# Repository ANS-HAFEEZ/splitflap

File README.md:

# Split-Flap Display

This is a DIY ESP32-based [split-flap display](https://en.wikipedia.org/wiki/Split-flap_display), optimized for easy assembly at home in small quantities but able to be scaled up to large affordable displays.

The [splitflap community Discord server](https://discord.com/invite/wgehm3PcrC) is the best place to keep up with the latest changes or ask questions about the project!

Want to help support development or just say "thanks"? Consider a one-time or monthly sponsorship:

| [:heart: Sponsor scottbez1 on GitHub](https://github.com/sponsors/scottbez1) |
|---|

**Using this project in a commercial setting or for paid client work?** Go right ahead - it's open source (just make sure to follow the terms of the Apache License)! I would, however, ask that you consider [sponsoring the project](https://github.com/sponsors/scottbez1). I've been developing and maintaining this project in my free time for over 10 years, and I'd love to continue working on it. Sponsorships allow me to pay for prototypes and development tools that make this project possible. Unlike pure software projects, every iteration has real hardware costs; sponsorships allow me to keep iterating and improving the project faster. Thank you!

# Current Status
[You can download the **latest stable releases** of the hardware designs from the official 'releases' page.](https://github.com/scottbez1/splitflap/releases)

Releases have been tested and used to produce working units, but as this is a continuously evolving open-source project, there may always be minor issues and/or incomplete documentation from time to time.

Here's a video of a large 108-module display powered by 18 Chainlink Driver boards and a Chainlink Base:

## Stable v2 Mechanical Release
As of 2025-01-19, the v2 refresh of the mechanical and sensor design is considered stable and recommended for new builds.

**Here's what's new in v2:**

- **40 flaps per module is the default configuration in this repository**
- **52-flap v2 modules remain supported** if you want additional symbols/color blocks
- **New printed flap design ("Epilogue")** with 52 flaps per set (see animation above), including several color-block flaps
- **Updated enclosure** and mechanical parts (laser-cut) to accomodate both 40- and 52-flap variants
  - Motor wires now exit downward for less awkward wiring!
- **New sensor PCB** that's easier to assemble and includes an LED for checking the magnet status
- **Software-configurable calibration** rather than mechanical sensor adjustment

**But many things are staying the same for easy upgrades/compatibility:**
- No change to flap dimensions!
- No changes to Chainlink Driver, Chainlink Buddy boards, or system architecture!
- 52-flap modules are still an officially supported option!
- Open source, as always!
- v0 parts (sensor kits) will continue to be stocked at Bezek Labs through mid-2025; don't worry if you haven't finished your build yet, the old sensor kits aren't going away for a little while!

I'd love to hear your thoughts and questions about this project, and happy to incorporate any feedback you might have into these designs! Please feel free (and encouraged) to [open GitHub issues](https://github.com/scottbez1/splitflap/issues/new), email me directly, reach out [on Bluesky](https://bsky.app/profile/scottbez1.bsky.social), and [get involved](https://github.com/scottbez1/splitflap/pulls) in the open source development and let's keep chatting and building together!

# Build Your Own
If you have any questions, please don't hesitate to ask in the [community Discord server](https://discord.gg/Hxnftc8PyW)!

* [**Documentation Index**](/docs/DocumentationIndex.md)
* [**Ordering guide (the "easy" route) v2**](/docs/v2/OrderingEasy.md)
* [**Comprehensive ordering guide**](/docs/v2/OrderingComplete.md)
* [**Chainlink Driver Electronics User Guide**](/docs/ElectronicsGuide.md)
* [**Assembly instructions v2**](/docs/v2/Assembly.md)
* [**Latest stable releases**](https://github.com/scottbez1/splitflap/releases)

# Table of Contents
- [Design Overview](#design-overview)
  - [Mechanical](#mechanical)
    - [Combined front panel (script)](#combined-front-panel-script)
    - [Flap font/sticker generator (script)](#flap-fontsticker-generator-script)
  - [Electronics](#electronics)
    - [Sensor PCBs](#sensor-pcbs-1-per-module)
    - [Chainlink Driver](#chainlink-driver-1-per-6-modules)
    - [Chainlink Buddy \[T-Display\]](#chainlink-buddy-t-display-1-for-entire-display)
    - [Advanced items](#advanced-items)
      - [Chainlink Buddy \[Breadboard\]](#chainlink-buddy-breadboard-1-for-entire-display-alternative-to-t-display)
      - [Chainlink Base](#chainlink-base-1-for-entire-display-large-displays)
    - [Older designs](#older-designs)
      - [Classic controller](#classic-controller-electronics-deprecated)
    + [Miscellaneous Tools](#miscellaneous-tools)
      - [3D Printed Tools](#3d-printed-tools)
      - [Chainlink Driver Tester](#chainlink-driver-tester)
  * [Code](#code)
    + [Firmware](#firmware)
    + [Computer Control Software](#computer-control-software)
- [Contributing/Modifying](#contributingmodifying)
  * [3D Design](#3d-design)
  * [Electronics Design](#electronics-design)

# Design Overview

## Mechanical
The mechanical/structural components are made from laser-cut 3mm MDF or acrylic, and held together with M4 bolts and nuts. The design is parametric and built using OpenSCAD. See below for more info on rendering/modifying the design.

You can view an interactive 3d model of the design [here](https://scottbez1.github.io/splitflap/embed.html?branch=master).

The v2 mechanical design officially supports both 40- and 52-flap variants (52 is perfect for use with the new ["Epilogue" printed flaps](https://bezeklabs.etsy.com/listing/1685633114/)). Repository defaults are configured for 40 flaps, but you can always override this.

### v2 (52-flap module option)

Instructions: [v2 assembly guide](/docs/v2/Assembly.md)

Module dimensions: 

Latest auto-generated (untested!) artifacts<sup>:warning:</sup>:
* For Ponoko 3mm MDF ([svg](https://s3.amazonaws.com/splitflap-artifacts/master/3d/3d_laser_vector-52-ponoko-3mm-mdf_1x.svg)) 
* For Ponoko 3mm acrylic ([svg](https://s3.amazonaws.com/splitflap-artifacts/master/3d/3d_laser_vector-52-ponoko-3mm-acrylic_1x.svg)) 
* For generic material (0.18mm kerf correction) ([svg](https://s3.amazonaws.com/splitflap-artifacts/master/3d/3d_laser_vector-52.svg))
* For Elecrow 3mm Wood ([zipped pdf](https://s3.amazonaws.com/splitflap-artifacts/master/3d/3d_laser_vector-52-elecrow-3mm-wood_1x.zip))
* For Elecrow 3mm Acrylic ([zipped pdf](https://s3.amazonaws.com/splitflap-artifacts/master/3d/3d_laser_vector-52-elecrow-3mm-acrylic_1x.zip))

<sup>:warning:</sup>For tested/stable/recommended artifacts, always use the [latest release](https://github.com/scottbez1/splitflap/releases) instead, as the links on this page will change over time.

### v2 (40-flap module option - default)

Instructions: [v2 assembly guide](/docs/v2/Assembly.md)

Module dimensions: 

Latest auto-generated (untested!) artifacts<sup>:warning:</sup>:
* For Ponoko 3mm MDF ([svg](https://s3.amazonaws.com/splitflap-artifacts/master/3d/3d_laser_vector-40-ponoko-3mm-mdf_1x.svg)) 
* For Ponoko 3mm acrylic ([svg](https://s3.amazonaws.com/splitflap-artifacts/master/3d/3d_laser_vector-40-ponoko-3mm-acrylic_1x.svg)) 
* For generic material (0.18mm kerf correction) ([svg](https://s3.amazonaws.com/splitflap-artifacts/master/3d/3d_laser_vector-40.svg))
* For Elecrow 3mm Wood ([zipped pdf](https://s3.amazonaws.com/splitflap-artifacts/master/3d/3d_laser_vector-40-elecrow-3mm-wood_1x.zip))
* For Elecrow 3mm Acrylic ([zipped pdf](https://s3.amazonaws.com/splitflap-artifacts/master/3d/3d_laser_vector-40-elecrow-3mm-acrylic_1x.zip))

<sup>:warning:</sup>For tested/stable/recommended artifacts, always use the [latest release](https://github.com/scottbez1/splitflap/releases) instead, as the links on this page will change over time.

### Combined front panel (script)
By default, the design will have a separate laser-cut faceplate for each individual module. For larger displays you may want to combine front panels into a single piece, and the repo has a script to help with this.

You can modify:
* Number of rows and columns
* Horizontal and vertical spacing/separation of modules
* Overall outer width and height of the panel

There are a lot of options; see the `--help` for explanations.

#### Example 1 - Laser cut 6x1

```
python3 3d/scripts/generate_combined_front_panel.py \
  --kerf-preset elecrow-3mm-acrylic \
  --num-flaps 40 \
  --cols 6 \
  --rows 1 \
  --spacing-x 0 \
  --spacing-y 0 \
  --frame-margin-x 0 \
  --frame-margin-y 0 \
  --center-mode module
```

#### Example 2 - CNC router 12x2, with frame margin

For CNC cutting, the script supports rendering a vector file optimized for thicker material (e.g. 6mm MDF) where only the bolt-holes will be through-cut. In this mode, the slots for the top/bottom enclosure pieces can be cut as ~4mm pockets so they aren't visible from the front face. The script automatically generates dog-bone shapes for these pocket cuts.

This example also demonstrates use of the --frame-margin-x and --frame-margin-y options to add an additional margin of 20mm horizontally and 4mm vertically to the front panel dimensions.

```
python3 3d/scripts/generate_combined_front_panel.py \
  --tool-diameter 3.175 \
  --num-flaps 40 \
  --cols 12 \
  --rows 2 \
  --spacing-x 0 \
  --spacing-y 0 \
  --frame-margin-x 20 \
  --frame-margin-y 4 \
  --center-mode module
```

### Flap font/sticker generator (script)
If you'd like to print your own flaps, or cut custom vinyl letter stickers, the project includes a script (`generate_fonts.py`) to generate vector design files, which is extremely configurable:

* Font for text
  * This is further customizable in `flap_fonts.scad` -- this is where font parameters are defined like the overall font scale, position offsets, and even per-character scale and position overrides in case you need to tweak particularly problematic letters (e.g. a really wide "W" or an "@" with too thin of a stroke).
* Character-set - which letters/numbers/symbols/colors are included and in what order
* Bleed - extends rendering past the borders of the flaps to compensate for slight misalignment of printing and cutting operations
* Keepout areas - option to highlight keepout violations for manual review, automatically clip them, or ignore them
* Rendering options:
    * Single-sided - useful for previewing how all letters will look on flaps
    * Front/back - for batch duplex printing, generate separate front-side and back-side files (e.g. sign shop printing on a flat sheet of PVC)
    * Side-by-side - for individual flap printing, each flap's front design is laid out side-by-side with its back design

There are a lot of options; see the `--help` for explanations.

#### Example 1 - Epilogue font, rendered in front+back pairs, default character set, 1mm bleed (for printing)

```
python3 3d/scripts/generate_fonts.py \
  --mode side-by-side \
  --font Epilogue \
  --columns 4 \
  --bleed 1 \
  --fill
```

## Electronics
> [!NOTE]
> For small displays (up to 3 modules), you can skip the custom controller boards and use off-the-shelf ULN2003A driver
modules plugged into an Arduino Uno. This is [partially documented in the wiki](https://github.com/scottbez1/splitflap/wiki/Electronics#basic-prototyping-alternative-electronics-approach)
> but may require some additional tinkering to get it to work. _Help wanted: if you'd like to help improve these instructions,
> please reach out in the Discord server, thanks!_

The "Chainlink" electronics system is designed to support long chains of driver boards to control medium/large displays (up to 100+ split-flap modules).
It's also designed to be easy and cheap to order pre-assembled or build yourself, especially in higher
quantities, due to its simple BOM and surface-mount components.

To build a display, you'll need 3 different electronics:
* One **Sensor PCB** for every split-flap module
* One **Chainlink Driver** board for every 6 split-flap modules. This is what interfaces with the motors and sensors of each module. Chainlink Driver boards can be chained together to construct a large display.
* An ESP32 microcontroller board. There are a few options:
    * For small/medium displays, one of the **Chainlink Buddy** boards are recommended
        * **Chainlink Buddy [T-Display]**  holds a Lilygo T-Display ESP32 module which includes a built-in LCD and 2 buttons
        * **Chainlink Buddy [Breadboard]** makes it easy to connect a Chainlink Driver to a breadboard for prototyping, though you can also easily connect a Chainlink Driver to a breadboard with a few dupont wires.
    * For large displays, the **Chainlink Base** provides a number of advanced features: central
power management/distribution and fault monitoring, UART and RS-485 connections, configuration switches, and status LEDs.

### Sensor PCBs (1 per module)
Each module needs a hall-effect sensor for start-up calibration and fault monitoring. 

#### Sensors v2

New sensors for the v2 laser-cut hardware - these use surface mount components and are optimized for PCB assembly at JLCPCB. These new sensors are not compatible with v0.7 and older laser-cut hardware.

Packs of 6 sensors are [available mostly-assembled in the Bezek Labs store](https://bezeklabs.etsy.com/listing/1696745674),
and come with the right-angle pin headers and magnets you'll need. Purchases support continued development of this project.

Latest auto-generated (untested!) artifacts<sup>:warning:</sup>:

* Schematic [pdf](https://s3.amazonaws.com/splitflap-artifacts/master/electronics-v2/sensor_smd-schematic.pdf)
* Interactive BOM (for manual assembly) [interactive](https://s3.amazonaws.com/splitflap-artifacts/master/electronics-v2/sensor_smd-ibom.html)
* Fabrication files (single)
  * NOTE: PCBs must be 0.8mm! (rather than the more typical 1.6mm thickness)
  * PCB gerbers [zip](https://s3.amazonaws.com/splitflap-artifacts/master/electronics-v2/sensor_smd-jlc/gerbers.zip)
  * PCB BOM (for JLCPCB assembly) [csv](https://s3.amazonaws.com/splitflap-artifacts/master/electronics-v2/sensor_smd-jlc/bom.csv)
  * PCB CPL (for JLCPCB assembly) [csv](https://s3.amazonaws.com/splitflap-artifacts/master/electronics-v2/sensor_smd-jlc/pos.csv)
* Fabrication files (panelized)
  * NOTE: PCBs must be 0.8mm! (rather than the more typical 1.6mm thickness)
  * PCB gerbers [zip](https://s3.amazonaws.com/splitflap-artifacts/master/electronics-v2/sensor_smd-panelized-jlc/gerbers.zip)
  * PCB BOM (for JLCPCB assembly) [csv](https://s3.amazonaws.com/splitflap-artifacts/master/electronics-v2/sensor_smd-panelized-jlc/bom.csv)
  * PCB CPL (for JLCPCB assembly) [csv](https://s3.amazonaws.com/splitflap-artifacts/master/electronics-v2/sensor_smd-panelized-jlc/pos.csv)
* Purchase sensor kits in the US: [Bezek Labs](https://bezeklabs.etsy.com/listing/1696745674)

<sup>:warning:</sup>For tested/stable/recommended artifacts, always use the [latest release](https://github.com/scottbez1/splitflap/releases) instead, as the links on this page will change over time.

### Chainlink Driver (1 per 6 modules)

Key features:
* Controls 6 split-flap modules per board
* Primarily SMD and all components (except the pin headers and motor connectors) are available in JLCPCB's parts library
for easy SMD/THT assembly
* Clock and latch lines are buffered on each board with a 74HC125 to support longer chains
* 2 bits of loopback error checking per board (connecting 2 spare output bits on output shift registers to 2 spare inputs) allows the controller
to validate data integrity up and down the whole chain
* Module order goes from right-to-left since this is intended to be installed and accessed from *behind* the modules

Chainlink Driver boards are [available mostly-assembled in the Bezek Labs store](https://bezeklabs.etsy.com/listing/1123280069/splitflap-chainlink-driver-v11),
and come with the additional connectors and ribbon cables you'll need. Purchases support continued development of this project.

More information on building and using Chainlink Drivers is available in the [Chainlink Driver User Guide](/docs/ElectronicsGuide.md).

Or if you'd like to order these directly from a fab, this design is optimized for assembly at JLCPCB, and files are automatically generated
for ordering *assembled* PCBs there. Or if you wish to assemble this board yourself instead of paying for assembly, 
you can view the [interactive BOM/placement tool](https://s3.amazonaws.com/splitflap-artifacts/master/electronics-chainlink/bom/chainlinkDriver-ibom.html)

Depending on available stock at JLCPCB, you may need to manually modify the BOM file to use alternative components, or regenerate the files
yourself using `export_jlcpcb.py` and specifying one or more `LCSC_ALT_*` field names to use a pre-selected alternative part number. See
the schematic for available pre-selected alternatives (check the symbol's properties/fields).

Latest auto-generated (untested!) artifacts<sup>:warning:</sup>:

* Schematic [pdf](https://s3.amazonaws.com/splitflap-artifacts/master/electronics-chainlink/chainlinkDriver-schematic.pdf)
* PCB overview [pdf](https://s3.amazonaws.com/splitflap-artifacts/master/electronics-chainlink/chainlinkDriver-pcb-packet.pdf)
* PCB gerbers [zip](https://s3.amazonaws.com/splitflap-artifacts/master/electronics-chainlink/chainlinkDriver-jlc/gerbers.zip)
* PCB bom (for JLCPCB assembly) [csv](https://s3.amazonaws.com/splitflap-artifacts/master/electronics-chainlink/chainlinkDriver-jlc/bom.csv)
* PCB CPL (for JLCPCB assembly) [csv](https://s3.amazonaws.com/splitflap-artifacts/master/electronics-chainlink/chainlinkDriver-jlc/pos.csv)
* PCB bom (for manual assembly) [interactive](https://s3.amazonaws.com/splitflap-artifacts/master/electronics-chainlink/bom/chainlinkDriver-ibom.html)

<sup>:warning:</sup>For tested/stable/recommended artifacts, always use the [latest release](https://github.com/scottbez1/splitflap/releases) instead, as the links on this page will change over time.

### Chainlink Buddy \[T-Display\] (1 for entire display)

The Chainlink Buddy \[T-Display\] is a convenient way to connect a T-Display ESP32 board (recommended microcontroller) to a chain
of Chainlink Drivers.

Key features:
* TTGO T-Display ESP32 module as the controller, which includes USB-C, color IPS LCD display and buttons
* Extra terminals for every pin of the T-Display allow you to connect any other peripherals to the ESP32 (the connection to the Chainlink Driver requires _only 4_ of the GPIOs)
* Optional barrel jack makes it easy to use a "wall wart" AC adapter/power-supply (since the Chainlink Driver only has screw terminals for power) -- plug in a 12V supply
and then run a wire from the onboard screw terminals to the Chainlink Driver's motor power screw terminals.
* Optional 5V regulator allows for powering the ESP32 without a USB connection, using the 12V motor power supply

Chainlink Buddy \[T-Display\] boards are [available in the Bezek Labs store](https://bezeklabs.etsy.com/listing/1109357786/splitflap-chainlink-buddy-t-display),
and come with the additional connectors you'll need. Purchases support continued development of this project. 

Latest auto-generated (untested!) artifacts<sup>:warning:</sup>:

* Schematic [pdf](https://s3.amazonaws.com/splitflap-artifacts/master/electronics-chainlink-buddy-t-display/chainlinkBuddyTDisplay-schematic.pdf)
* PCB ([gerbers](https://s3.amazonaws.com/splitflap-artifacts/master/electronics-chainlink-buddy-t-display/chainlinkBuddyTDisplay-jlc/gerbers.zip) / [pdf](https://s3.amazonaws.com/splitflap-artifacts/master/electronics-chainlink-buddy-t-display/chainlinkBuddyTDisplay-pcb-packet.pdf))
* Panelized PCB ([gerbers](https://s3.amazonaws.com/splitflap-artifacts/master/electronics-chainlink-buddy-t-display/chainlinkBuddyTDisplay-panelized-jlc/gerbers.zip) / [pdf](https://s3.amazonaws.com/splitflap-artifacts/master/electronics-chainlink-buddy-t-display/chainlinkBuddyTDisplay-panelized-pcb-packet.pdf))
* PCB bom (for manual assembly) [interactive](https://s3.amazonaws.com/splitflap-artifacts/master/electronics-chainlink-buddy-t-display/bom/chainlinkBuddyTDisplay-ibom.html)

<sup>:warning:</sup>For tested/stable/recommended artifacts, always use the [latest release](https://github.com/scottbez1/splitflap/releases) instead, as the links on this page will change over time.

### Advanced items
#### Chainlink Buddy \[Breadboard\] (1 for entire display; alternative to T-Display)

The Chainlink Buddy \[Breadboard\] makes it easy to connect a Chainlink Driver to a breadboard for prototyping. You could use 5 dupont wires and have a
messy rats nest, or you could use a single ribbon cable and this slick breakout board.

Chainlink Buddy \[Breadboard\] boards are [available in the Bezek Labs store](https://bezeklabs.etsy.com/listing/1123863267/splitflap-chainlink-buddy-breadboard),
and come with the additional connectors you'll need. Purchases support continued development of this project. 

Latest auto-generated (untested!) artifacts<sup>:warning:</sup>:

* Schematic [pdf](https://s3.amazonaws.com/splitflap-artifacts/master/electronics-chainlink-buddy-breadboard/chainlinkBuddyBreadboard-schematic.pdf)
* PCB ([gerbers](https://s3.amazonaws.com/splitflap-artifacts/master/electronics-chainlink-buddy-breadboard/chainlinkBuddyBreadboard-jlc/gerbers.zip) / [pdf](https://s3.amazonaws.com/splitflap-artifacts/master/electronics-chainlink-buddy-breadboard/chainlinkBuddyBreadboard-pcb-packet.pdf))
* Panelized PCB ([gerbers](https://s3.amazonaws.com/splitflap-artifacts/master/electronics-chainlink-buddy-breadboard/chainlinkBuddyBreadboard-panelized-jlc/gerbers.zip) / [pdf](https://s3.amazonaws.com/splitflap-artifacts/master/electronics-chainlink-buddy-breadboard/chainlinkBuddyBreadboard-panelized-pcb-packet.pdf))
* PCB bom (for manual assembly) [interactive](https://s3.amazonaws.com/splitflap-artifacts/master/electronics-chainlink-buddy-breadboard/bom/chainlinkBuddyBreadboard-ibom.html)

<sup>:warning:</sup>For tested/stable/recommended artifacts, always use the [latest release](https://github.com/scottbez1/splitflap/releases) instead, as the links on this page will change over time.

#### Chainlink Base (1 for entire display; large displays)

For larger displays, you should take additional care to make the hardware more robust to potential faults. The Chainlink Base is an experimental (but unsupported) controller design that adds some additional functionality. This has been tested and appears to work, but is not recommended for general use.

The Chainlink Base PCB is an optional alternative to a Chainlink Buddy, designed for particularly large displays.
It hosts the ESP32 and adds additional connectivity options (terminals for UART and RS485 serial) and
power distribution (independently-monitored power channels for multiple "zones" of Driver boards).

Key features:
* TTGO T-Display ESP32 module as the controller, which includes USB-C, color IPS LCD display and buttons
* Optional master relay output for 12V PSU control (5V relay, up to ~500mA coil current)
  * Future firmware will power on the 12V PSU after a startup self-test, and power off PSU in case of any faults
* 5 channels of independently monitored 12V switches for powering groups of Chainlink Driver boards (6-10A max per channel)
  * Depending on the motors you use, each channel may be able to power about 6 Chainlink Driver boards which is 36 splitflap modules
  * Each channel includes an automotive fuse holder for additional over-current protection
  * INA219 and shunt resistor provide high fidelity voltage and current monitoring 
  * Firmware will power on each channel after a startup self-test, and power off the channel in case of any faults
  * 3.3V output for powering many Chainlink Driver boards
* Flexible controller input power
  * USB power from the T-Display works by default, though external power is recommended for larger displays
  * Regulated 5V can be connected directly to the screw terminals, or
  * if you are using an always-on 12V PSU without a master relay, you can install a buck module and power the board from 12V using the 7-28V screw terminals

Latest auto-generated (untested!) artifacts<sup>:warning:</sup>:

* Schematic [pdf](https://s3.amazonaws.com/splitflap-artifacts/master/electronics-chainlink-base/chainlinkBase-schematic.pdf)
* PCB overview [pdf](https://s3.amazonaws.com/splitflap-artifacts/master/electronics-chainlink-base/chainlinkBase-pcb-packet.pdf)
* PCB gerbers [zip](https://s3.amazonaws.com/splitflap-artifacts/master/electronics-chainlink-base/chainlinkBase-jlc/gerbers.zip)
* PCB bom (for manual assembly) [interactive](https://s3.amazonaws.com/splitflap-artifacts/master/electronics-chainlink-base/bom/chainlinkBase-ibom.html)

<sup>:warning:</sup>There are currently no stable releases of this board, and none are planned. Some past variants of this board have been used, to some success, but it is not considered an
officially supported design

## Older designs
### Classic Controller Electronics (deprecated)
The Classic driver board is deprecated and unsupported.

The Classic controller board was designed to plug into an Arduino like a shield, and could control 4 stepper motors.
Up to 3 driver boards could be chained together, for up to 12 modules controlled by a single Arduino.

The driver uses 2 MIC5842 low-side shift-register drivers, with built-in transient-suppression diodes, to control the motors, and a 74HC165 shift register to read from 4 hall-effect magnetic home position sensors.
There are optional WS2812B RGB LEDs which can be used to indicate the status of each of the 4 channels.

### Miscellaneous Tools

#### 3D Printed Tools
The project also includes a number of optional 3D printed designs to make assembly easier. These include:

* [a flap scoring jig](3d/tools/scoring_jig.scad) for precisely marking the cut point when splitting CR80 cards
* [a flap punch jig](3d/tools/punch_jig.scad) for aligning the punch when making the pin cutouts on either side of a flap
* [a flap container](3d/tools/flap_container.scad) for storing and organizing stacks of completed flaps

All of these designs are parametric and customizable within OpenSCAD. To print them, open up the relevant file in OpenSCAD and use `File -> Export -> Export as STL` to render the design as an STL file for your slicer.

#### Chainlink Driver Tester

This is not likely to be useful unless you're planning to manufacture dozens to hundreds of Chainlink Driver boards, but the Chainlink Driver Tester is a complete testbed
for Chainlink Driver boards as they come assembled by the PCBA fabricator.

This is currently under very active development.

Key features:
* TTGO T-Display (ESP32) controller, screen, and buttons for controlling tests and reporting results
* Pogo-pins for all connectors on the Chainlink Driver board-under-test (screw terminals, sensor pin headers, and motor connectors)
* 12V switch to supply motor power to the board-under-test, with automotive fuse and INA219 voltage/current monitoring (based on the Chainlink Base channel switch design)
* Separate 3.3V supply for the board-under-test, protected with a polyfuse, should avoid browning out the Tester's MCU in case of 3.3V short-circuits
* Motor and sensor connections are broken out from the pogo-pins for a full closed-loop hardware test
* Screw terminals to chain another Chainlink Driver (not under test) to validate that chained outputs work on the board-under-test
* MCP23017 GPIO expander with 8 GPIO pins exposed via headers for future expansion inputs
* Large cutout allows a barcode scanner or camera to be aimed at the bottom of the board-under-test for tracking serial numbers.
* Buzzer option for audible pass/fail feedback

Latest auto-generated (untested!) artifacts<sup>:warning:</sup>:

* Schematic [pdf](https://s3.amazonaws.com/splitflap-artifacts/master/electronics-chainlink-tester/chainlinkDriverTester-schematic.pdf)
* PCB overview [pdf](https://s3.amazonaws.com/splitflap-artifacts/master/electronics-chainlink-tester/chainlinkDriverTester-pcb-packet.pdf)
* PCB gerbers [zip](https://s3.amazonaws.com/splitflap-artifacts/master/electronics-chainlink-tester/chainlinkDriverTester-jlc/gerbers.zip)
* PCB bom (for manual assembly) [interactive](https://s3.amazonaws.com/splitflap-artifacts/master/electronics-chainlink-tester/bom/chainlinkDriverTester-ibom.html)

<sup>:warning:</sup>There are currently no stable releases of this board, and there may never be as it is a niche production tool, not an end product. If you
need this tool, you are likely actively involved in development and should understand the revision history and current status of development enough to make
an informed decision about which revision(s) to use.

## Code
### Firmware
The driver firmware is written using PlatformIO with the Arduino framework and is available at [`firmware/`](firmware/). 

The firmware implements a closed-loop controller that accepts letters as input over USB serial and drives the stepper motors using a precomputed acceleration ramp for smooth control. The firmware automatically calibrates the spool position at startup, using the hall-effect magnetic sensor, and will automatically recalibrate itself if it ever detects that the spool position has gotten out of sync. If a commanded rotation is expected to bring the spool past the "home" position, it will confirm that the sensor is triggered neither too early nor too late; otherwise it will search for the "home" position to get in sync before continuing to the desired letter.

### Serial protocol
In order for a computer to communicate with the splitflap, it appears as a USB serial device.

However, usage of Arduino’s `Serial` is strictly forbidden, and instead a `logger` abstraction is provided for sending basic text debug logs. Other data is transferred in a structured way, described below.

This allows flexibility in the format of data transferred over serial, and in fact the splitflap provides 2 different serial modes that serve different purposes.

#### Plaintext mode

By default, it starts in “plaintext” mode, which is developer-friendly and you’re probably familiar with if you’ve opened a serial monitor with the splitflap connected:
```
{"type":"init", "num_modules":6}
```

However, this isn’t great for programmatically configuring or receiving updates from the splitflap, so instead the firmware offers a programmatic interface using a binary protocol based on Google’s Protobuf standard.

#### Protobuf (binary/programmatic) mode

The protobuf-based binary serial mode is a compact and flexible way to transfer structured data from the host computer to the splitflap and vice-versa.

##### Benefits of protobuf
protobuf provides several benefits over other encoding mechanisms like JSON:

1. Well-defined schema. If you’re curious about the format of data to expect or send, you just need to check the protobuf file
2. Code generation. Instead of hand-writing JSON parsers every time the data changes, protobuf provides code generation of the encoding and decoding logic, and data-structures. Splitflap uses nanopb to generate C structs based off the schema, and all the code for encoding/decoding that data from the binary format.
3. Relatively compact/efficient wire encoding. It’s not a primary goal in this project, but the binary wire encoding is generally fairly compact, due to omitting default/unspecified fields, using variable length encodings, etc. It’s certainly much more compact than JSON which uses strings to describe every field in every message.
4. Backwards/forwards compatibility. Not super relevant to this project, but many common schema changes are backwards and forwards compatible, meaning an older client or a newer client will be able to handle them gracefully.

##### Disadvantages of protobuf

1. Not human-readable. This makes it much harder to debug, as you need something that can interpret messages. Since they’re binary, viewing anything in a terminal directly will be fruitless.
2. Not self-describing. If you come across a JSON document, you can generally tell what it means because fields have string names/labels describing their contents. Protobuf has no such thing (it uses integer field numbers, which does make renaming fields easier) so you need to have a copy of the schema (.proto file - and you’d better hope it matches the data!) in order to understand an encoded message.

This is why the splitflap defaults to plaintext mode to make basic validation/debugging easier.

##### How it works
Protobuf messages are encoded to their binary wire format and a CRC32 checksum appended. Then that entire binary string is COBS encoded into a packet, and delimited/framed by 0 (NULL) bytes when sent over serial. This provides a basic packet-based interface with integrity checks (rather than the raw, stream-based interface of a serial connection).

The splitflap automatically switches to binary protobuf mode when it receives a 0 byte.

### Computer Control Software
The display can be controlled by a computer connected to the ESP32 over USB serial. If you've built a display and want to test it out, check out the web-based demo [here](https://scottbez1.github.io/splitflap) which will connect to your display using USB - no applications/installation necessary!

The firmware supports a plaintext serial mode (enabled by default) for ease of testing, and a protobuf-based binary mode used by the software libraries for enhanced programmatic control and feedback.

You can find example Typescript and Python libraries in the [`software/chainlink`](software/chainlink) folder.

# Contributing/Modifying

Looking to make some modifications or play around with the design on your local machine? Jump right in! Note that all of the scripts and automation are developed for Ubuntu. Mac OS support is planned,
but not currently implemented (but feel free to open a PR if you want to help!).

## 3D Design

The main design file is [`3d/splitflap.scad`](3d/splitflap.scad)

You'll need a recent version of OpenSCAD (e.g. 2015-03), which may need to be installed through the PPA:
`sudo add-apt-repository ppa:openscad/releases`

In general, solid objects such as the enclosure sides or spool components are built from 2d primitives and then extruded to the appropriate thickness for 3d rendering, rather than using 3d primitives. This simplifies the design without losing expressiveness; the perpendicular laser cut beam doesn't allow for cuts that vary in the Z dimension anyway.

Note that while the design is parameterized and many values may be tweaked, there is currently no error checking for invalid parameters or combinations of parameters. Please take care to validate the design if you change any parameters. For instance, while most of the design will adjust to a changed `num_modules` value, certain values may cause some elements to intersect with other elements or protrude beyond their expected dimensions.

### Rendering
#### Laser-cut vector files
The design can be rendered to 2d for laser cutting by running [`3d/scripts/generate_2d.py [--panelize <number>]`](3d/scripts/generate_2d.py), which outputs to `3d/build/laser_parts/combined.svg`. The optional `--panelize` argument allows for rendering a panel of modules in a single SVG, for bulk laser-cutting.

Internally, the design uses a `projection_renderer` module ([`3d/projection_renderer.scad`](3d/projection_renderer.scad)), which takes a list of child elements to render, and depending on the `render_index` renders a single child at a time. It also _adds_ material to each shape to account for the kerf that will be cut away by the laser.

The [`generate_2d.py`](3d/scripts/generate_2d.py) script interacts with the `projection_renderer` module by first using it to determine the number of subcomponents to render, then runs OpenSCAD to export each component to an SVG file. It does some post-processing on the SVG output (notably adds "mm" to the document dimensions), and then combines all components into the single `combined.svg` output.

Once the `combined.svg` file is generated, you'll want to double-check there aren't any redundant cut lines that are shared by multiple adjacent pieces, to save time/cost when cutting. They should be detected automatically (and highlighted in red in the rendering above), but it doesn't hurt to double-check. In Inkscape, select the "Edit paths by nodes" tool and select an edge to delete - the endpoints should turn blue. Then click "Delete segment between two non-endpoint nodes", and repeat this for all other redundant cut lines.

#### Animated gif
The design can be rendered to a rotating 3d animated gif (seen above) by running [`3d/scripts/generate_gif.py`](3d/scripts/generate_gif.py), which outputs to `3d/build/animation/animation.gif`

The `generate_gif.py` script runs multiple OpenSCAD instances in parallel to render the design from 360 degrees to individual png frames, which are then combined into the final gif animation. As part of building the animation, `generate_gif.py` renders the design with multiple configurations (opaque enclosure, see-through enclosure, no-enclosure and no flaps) by setting the `render_enclosure` and `render_flaps` variables.

#### STL models/web viewer
The design can be rendered to a series of STL files (one per color used in the model) in order to be displayed in an [interactive web-based 3d viewer](https://scottbez1.github.io/splitflap/). Similar to the `projection_renderer` used to render individual components for laser-cutting, the [ColoredStlExporter](3d/scripts/colored_stl_exporter.py) detects all the colors used in the model and renders them one-by-one to separate STL files, along with a manifest that maps each STL file to its RGB color. The STL files and manifest are loaded using three.js to display an interactive model on a web site using WebGL. See this blog post for more details on how the export and three.js renderer work: [OpenSCAD Rendering Tricks, Part 3: Web viewer](http://scottbezek.blogspot.com/2016/08/openscad-rendering-tricks-part-3-web.html).

## Electronics Design
All of the electronics are developed using KiCad 5. Panelization is provided by [KiKit](https://github.com/yaqwsx/KiKit) and gerber/BOM generation is provided by [KiBot](https://github.com/INTI-CMNB/KiBot).

### Rendering
The mechanical and electrical design renderings and links above are automatically updated on every commit with the latest rendering. See this blog post for more details on how that works: [Automated KiCad, OpenSCAD rendering using Travis CI](http://scottbezek.blogspot.com/2016/04/automated-kicad-openscad-rendering.html).

The PCB layout can be rendered to an svg or png (seen above) by running [`electronics/scripts/generate_svg.py file.kicad_pcb`](electronics/scripts/generate_svg.py).
This uses KiCad's [Python scripting API](https://docs.kicad-pcb.org/doxygen/md_Documentation_development_pcbnew-plugins.html)
to render several layers to individual svg files, manipulates them to apply color and opacity settings, and then merges them to a single svg.
For additional details, see this blog post: [Scripting KiCad Pcbnew exports](http://scottbezek.blogspot.com/2016/04/scripting-kicad-pcbnew-exports.html).

For reviewing the design, a pdf packet with copper, silkscreen, and drill info can be produced by running [`electronics/scripts/generate_pdf.py file.kicad_pcb`](electronics/scripts/generate_pdf.py).

Gerber files for fabrication can be exported by running [`electronics/scripts/generate_gerber.py file.kicad_pcb`](electronics/scripts/generate_gerber.py).
This generates gerber files and an Excellon drill file with Seeed Studio's [naming conventions](http://support.seeedstudio.com/knowledgebase/articles/1176532-how-to-generate-the-gerber-manufacturing-files) and produces a `.zip` which can be sent for fabrication.

EESchema isn't easily scriptable, so to export the schematic [`electronics/scripts/export_schematic.py`](electronics/scripts/export_schematic.py) starts an X Virtual Frame Buffer (Xvfb) and open the `eeschema` GUI within that virtual display, and then send a series of hardcoded key presses via `xdotool` to interact with the GUI and click through the dialogs. This is very fragile but seems to work ok for now. For additional details, see this blog post: [Using UI automation to export KiCad schematics](http://scottbezek.blogspot.com/2016/04/automated-kicad-schematic-export.html).

# License
I'd love to hear your thoughts and questions about this project, and happy to incorporate any feedback you might have into these designs! Please feel free (and encouraged) to [open GitHub issues](https://github.com/scottbez1/splitflap/issues/new), email me directly, reach out [on Twitter](https://twitter.com/scottbez1), and [get involved](https://github.com/scottbez1/splitflap/pulls) in the open source development and let's keep chatting and building together!

This project is licensed under Apache v2 (see [LICENSE.txt](LICENSE.txt)).

    Copyright 2015-2025 Scott Bezek and the splitflap contributors
    
    Licensed under the Apache License, Version 2.0 (the "License");
    you may not use this file except in compliance with the License.
    You may obtain a copy of the License at
    
        http://www.apache.org/licenses/LICENSE-2.0
    
    Unless required by applicable law or agreed to in writing, software
    distributed under the License is distributed on an "AS IS" BASIS,
    WITHOUT WARRANTIES OR CONDITIONS OF ANY KIND, either express or implied.
    See the License for the specific language governing permissions and
    limitations under the License.

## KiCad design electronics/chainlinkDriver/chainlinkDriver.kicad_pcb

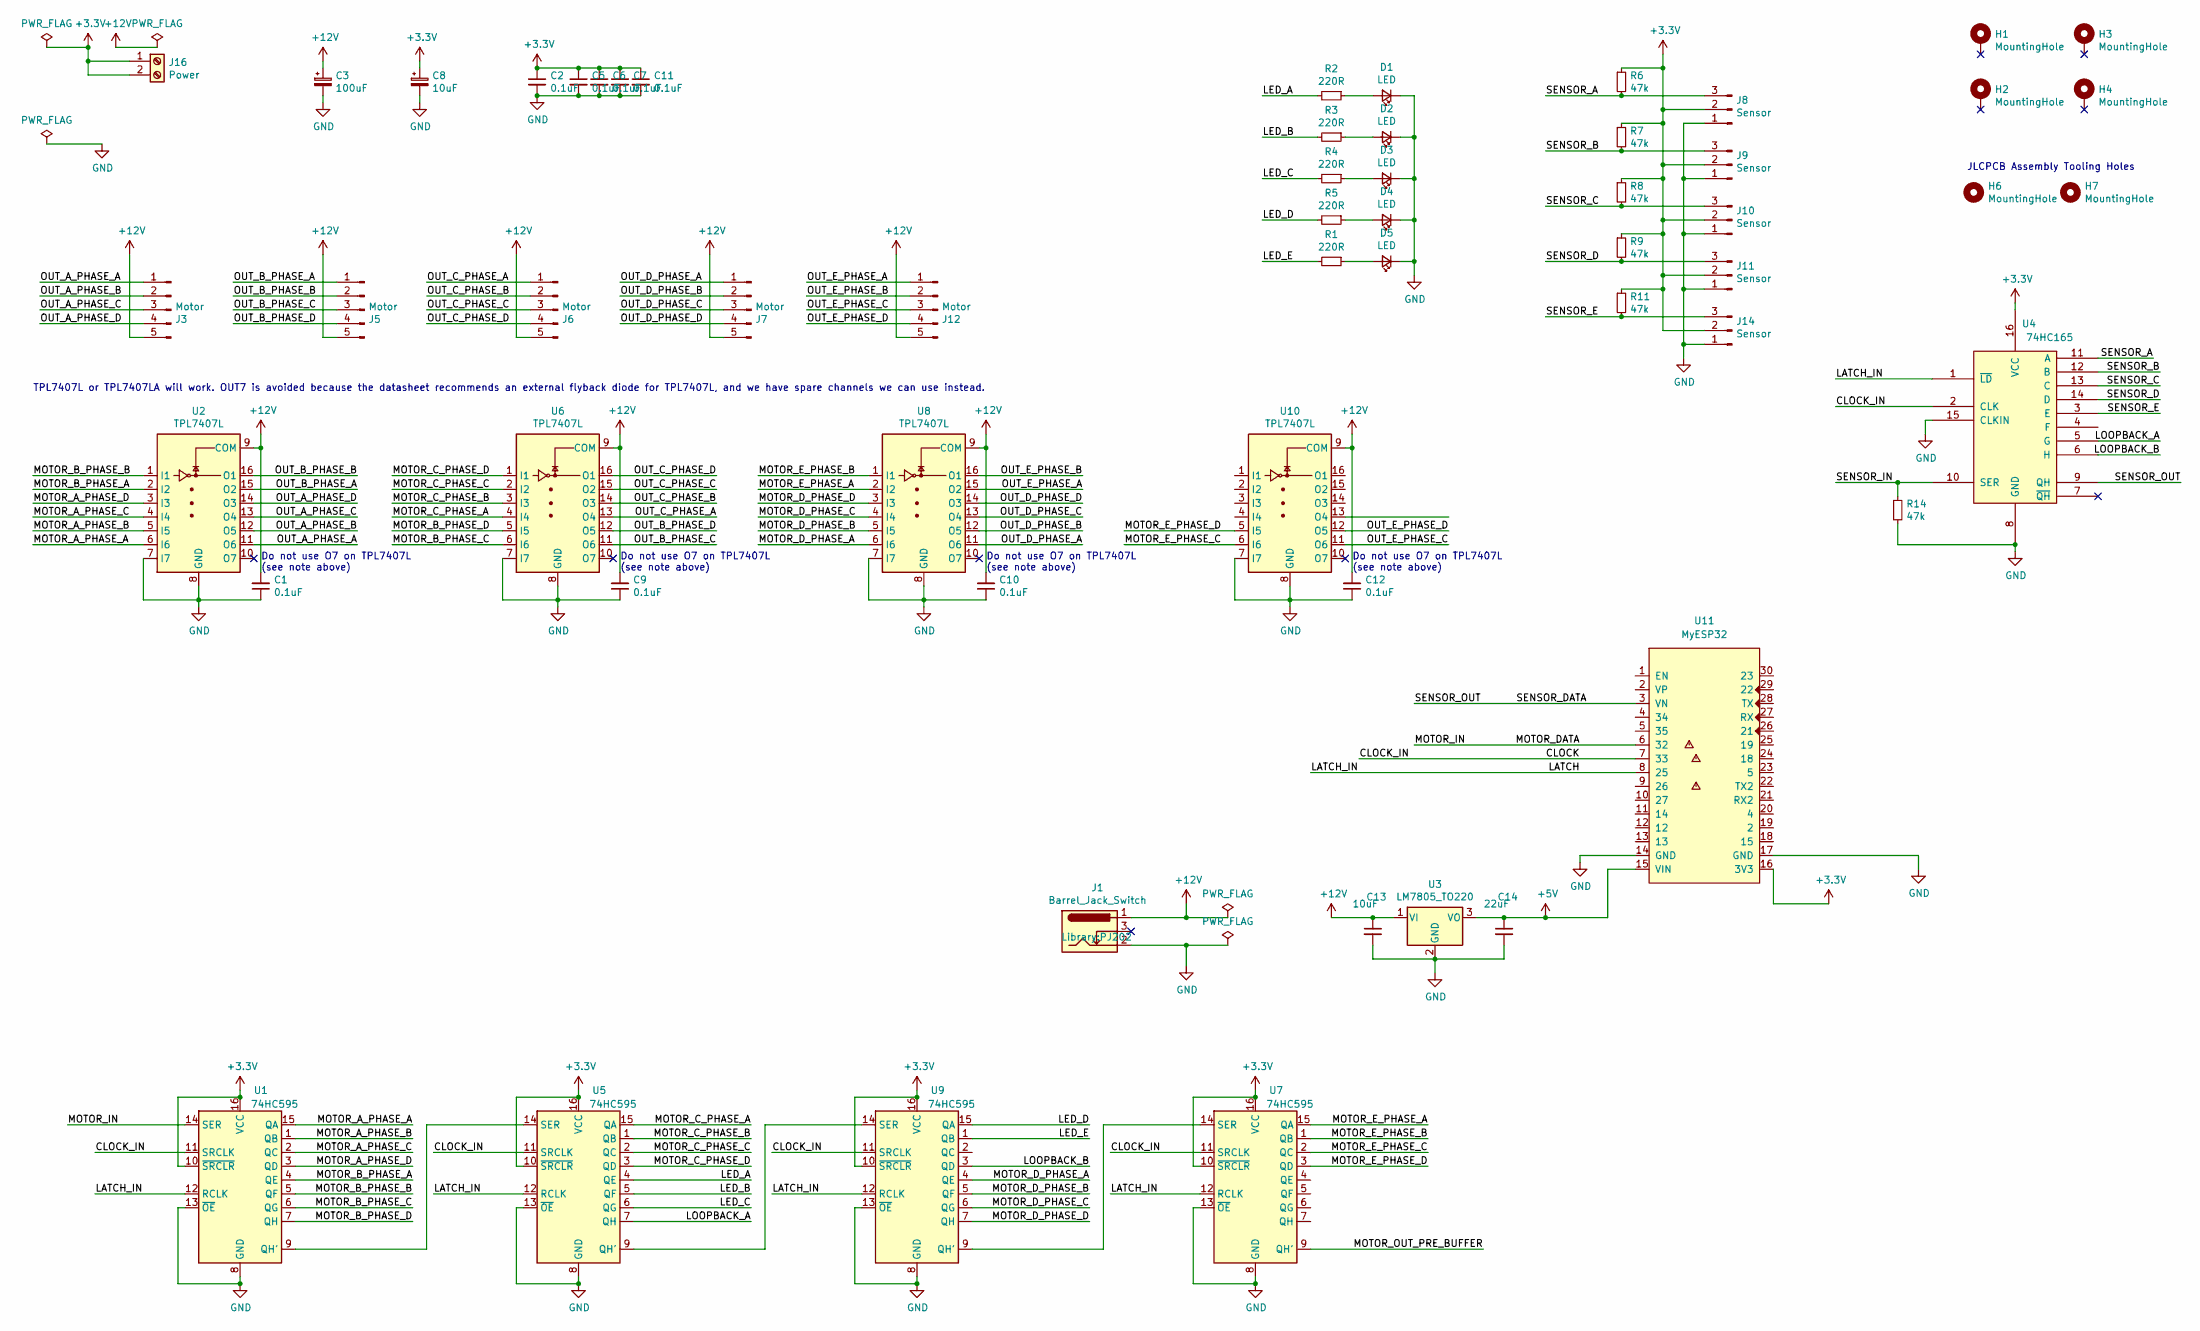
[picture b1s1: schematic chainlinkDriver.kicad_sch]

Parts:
C1, C2, C5, C6, C7, C9, C10, C11, C12: 0.1uF; C_0603_1608Metric; LCSC C14663
C3: 100uF; CP_Elec_8x10; LCSC C176665
C8: 10uF; CP_Elec_4x5.3; LCSC C176661
C13: 10uF; C_1206_3216Metric_Pad1.33x1.80mm_HandSolder
C14: 22uF; C_1206_3216Metric_Pad1.33x1.80mm_HandSolder
D1, D2, D3, D4, D5: LED; LED_0603_1608Metric_Silkscreen; LCSC C2286
H1, H2, H3, H4: MountingHole; MountingHole_3.2mm_M3_ISO7380_Pad
H6, H7: MountingHole; AssemblyToolingHole
J1: Barrel_Jack_Switch; PJ202
J3, J5, J6, J7, J12: Motor; JST_XH_B5B-XH-A_1x05_P2.50mm_Vertical; LCSC C157991
J8, J9, J10, J11, J14: Sensor; PinHeader_1x03_P2.54mm_Vertical; LCSC C49257
J16: Power; Generic-5.08-2P; LCSC C8465
R1, R2, R3, R4, R5: 220R; R_0603_1608Metric; LCSC C22962
R6, R7, R8, R9, R11, R14: 47k; R_0603_1608Metric; LCSC C25819
U1, U5, U7, U9: 74HC595; SOIC-16_3.9x9.9mm_P1.27mm_silk; LCSC C5947
U2, U6, U8, U10: TPL7407L; SOIC-16_3.9x9.9mm_P1.27mm_silk; LCSC C139663
U3: LM7805_TO220; TO-220-3_Vertical
U4: 74HC165; SOIC-16_3.9x9.9mm_P1.27mm_silk; LCSC C5613
U11: MyESP32

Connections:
+3.3V: C2.1, C5.1, C6.1, C7.1, C8.1, C11.1, J8.2, J9.2, J10.2, J11.2, J14.2, J16.1, J16.2, R6.1, R7.1, R8.1, R9.1, R11.1, U1.10 (~SRCLR), U1.16 (VCC), U4.16 (VCC), U5.10 (~SRCLR), U5.16 (VCC), U7.10 (~SRCLR), U7.16 (VCC), U9.10 (~SRCLR), U9.16 (VCC), U11.16 (3V3)
+5V: C14.1, U3.3 (VO), U11.15 (VIN)
+12V: C1.2, C3.1, C9.2, C10.2, C12.2, C13.1, J1.1, J3.5, J5.5, J6.5, J7.5, J12.5, U2.9 (COM), U3.1 (VI), U6.9 (COM), U8.9 (COM), U10.9 (COM)
/CLOCK: U1.11 (SRCLK), U4.2 (CLK), U5.11 (SRCLK), U7.11 (SRCLK), U9.11 (SRCLK), U11.7 (33)
/LATCH: U1.12 (RCLK), U4.1 (~LD), U5.12 (RCLK), U7.12 (RCLK), U9.12 (RCLK), U11.8 (25)
/LED_A: R2.2, U5.4 (QE)
/LED_B: R3.2, U5.5 (QF)
/LED_C: R4.2, U5.6 (QG)
/LED_D: R5.2, U9.15 (QA)
/LED_E: R1.2, U9.1 (QB)
/LOOPBACK_A: U4.5 (G), U5.7 (QH)
/LOOPBACK_B: U4.6 (H), U9.3 (QD)
/MOTOR_A_PHASE_A: U1.15 (QA), U2.6 (I6)
/MOTOR_A_PHASE_B: U1.1 (QB), U2.5 (I5)
/MOTOR_A_PHASE_C: U1.2 (QC), U2.4 (I4)
/MOTOR_A_PHASE_D: U1.3 (QD), U2.3 (I3)
/MOTOR_B_PHASE_A: U1.4 (QE), U2.2 (I2)
/MOTOR_B_PHASE_B: U1.5 (QF), U2.1 (I1)
/MOTOR_B_PHASE_C: U1.6 (QG), U6.6 (I6)
/MOTOR_B_PHASE_D: U1.7 (QH), U6.5 (I5)
/MOTOR_C_PHASE_A: U5.15 (QA), U6.4 (I4)
/MOTOR_C_PHASE_B: U5.1 (QB), U6.3 (I3)
/MOTOR_C_PHASE_C: U5.2 (QC), U6.2 (I2)
/MOTOR_C_PHASE_D: U5.3 (QD), U6.1 (I1)
/MOTOR_DATA: U1.14 (SER), U11.6 (32)
/MOTOR_D_PHASE_A: U8.6 (I6), U9.4 (QE)
/MOTOR_D_PHASE_B: U8.5 (I5), U9.5 (QF)
/MOTOR_D_PHASE_C: U8.4 (I4), U9.6 (QG)
/MOTOR_D_PHASE_D: U8.3 (I3), U9.7 (QH)
/MOTOR_E_PHASE_A: U7.15 (QA), U8.2 (I2)
/MOTOR_E_PHASE_B: U7.1 (QB), U8.1 (I1)
/MOTOR_E_PHASE_C: U7.2 (QC), U10.6 (I6)
/MOTOR_E_PHASE_D: U7.3 (QD), U10.5 (I5)
/MOTOR_OUT_PRE_BUFFER: U7.9 (QH')
/OUT_A_PHASE_A: J3.1, U2.11 (O6)
/OUT_A_PHASE_B: J3.2, U2.12 (O5)
/OUT_A_PHASE_C: J3.3, U2.13 (O4)
/OUT_A_PHASE_D: J3.4, U2.14 (O3)
/OUT_B_PHASE_A: J5.1, U2.15 (O2)
/OUT_B_PHASE_B: J5.2, U2.16 (O1)
/OUT_B_PHASE_C: J5.3, U6.11 (O6)
/OUT_B_PHASE_D: J5.4, U6.12 (O5)
/OUT_C_PHASE_A: J6.1, U6.13 (O4)
/OUT_C_PHASE_B: J6.2, U6.14 (O3)
/OUT_C_PHASE_C: J6.3, U6.15 (O2)
/OUT_C_PHASE_D: J6.4, U6.16 (O1)
/OUT_D_PHASE_A: J7.1, U8.11 (O6)
/OUT_D_PHASE_B: J7.2, U8.12 (O5)
/OUT_D_PHASE_C: J7.3, U8.13 (O4)
/OUT_D_PHASE_D: J7.4, U8.14 (O3)
/OUT_E_PHASE_A: J12.1, U8.15 (O2)
/OUT_E_PHASE_B: J12.2, U8.16 (O1)
/OUT_E_PHASE_C: J12.3, U10.11 (O6)
/OUT_E_PHASE_D: J12.4, U10.12 (O5)
/SENSOR_A: J8.3, R6.2, U4.11 (A)
/SENSOR_B: J9.3, R7.2, U4.12 (B)
/SENSOR_C: J10.3, R8.2, U4.13 (C)
/SENSOR_D: J11.3, R9.2, U4.14 (D)
/SENSOR_DATA: U4.9 (QH), U11.3 (VN)
/SENSOR_E: J14.3, R11.2, U4.3 (E)
/SENSOR_IN: R14.1, U4.10 (SER)
GND: C1.1, C2.2, C3.2, C5.2, C6.2, C7.2, C8.2, C9.1, C10.1, C11.2, C12.1, C13.2, C14.2, D1.1 (K), D2.1 (K), D3.1 (K), D4.1 (K), D5.1 (K), J1.2, J8.1, J9.1, J10.1, J11.1, J14.1, R14.2, U1.8 (GND), U1.13 (~OE), U2.7 (I7), U2.8 (GND), U3.2 (GND), U4.8 (GND), U4.15 (CLKIN), U5.8 (GND), U5.13 (~OE), U6.7 (I7), U6.8 (GND), U7.8 (GND), U7.13 (~OE), U8.7 (I7), U8.8 (GND), U9.8 (GND), U9.13 (~OE), U10.7 (I7), U10.8 (GND), U11.14 (GND), U11.17 (GND)
unnamed: D1.2 (A), R2.1
unnamed: D2.2 (A), R3.1
unnamed: D3.2 (A), R4.1
unnamed: D4.2 (A), R5.1
unnamed: D5.2 (A), R1.1
unnamed: U1.9 (QH'), U5.14 (SER)
unnamed: U5.9 (QH'), U9.14 (SER)
unnamed: U7.14 (SER), U9.9 (QH')

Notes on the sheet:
Do not use O7 on TPL7407L (see note above)
TPL7407L or TPL7407LA will work. OUT7 is avoided because the datasheet recommends an external flyback diode for TPL7407L, and we have spare channels we can use instead.
JLCPCB Assembly Tooling Holes

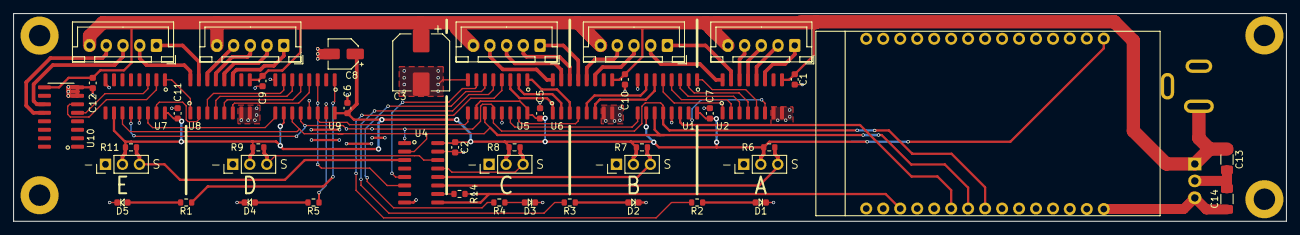
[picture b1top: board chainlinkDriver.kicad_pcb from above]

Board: 2 copper layers, 190.4 x 31.1 mm, 55 parts (0 on the bottom side), 69 nets.

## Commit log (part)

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2026-03-15 design update
2026-04-17 Add KiCad projects and MQTT calibrate feature
2026-04-18 Wifi manager added
2026-04-18 Add decrease-by-1/10 calibration command
2026-04-18 Add Chainlink KiCad schematics and libs
2026-04-21 Enable Gerber, update PCB routing & local settings
2026-05-09 Replace MQTT task with HTTP server task
2026-05-13 save
